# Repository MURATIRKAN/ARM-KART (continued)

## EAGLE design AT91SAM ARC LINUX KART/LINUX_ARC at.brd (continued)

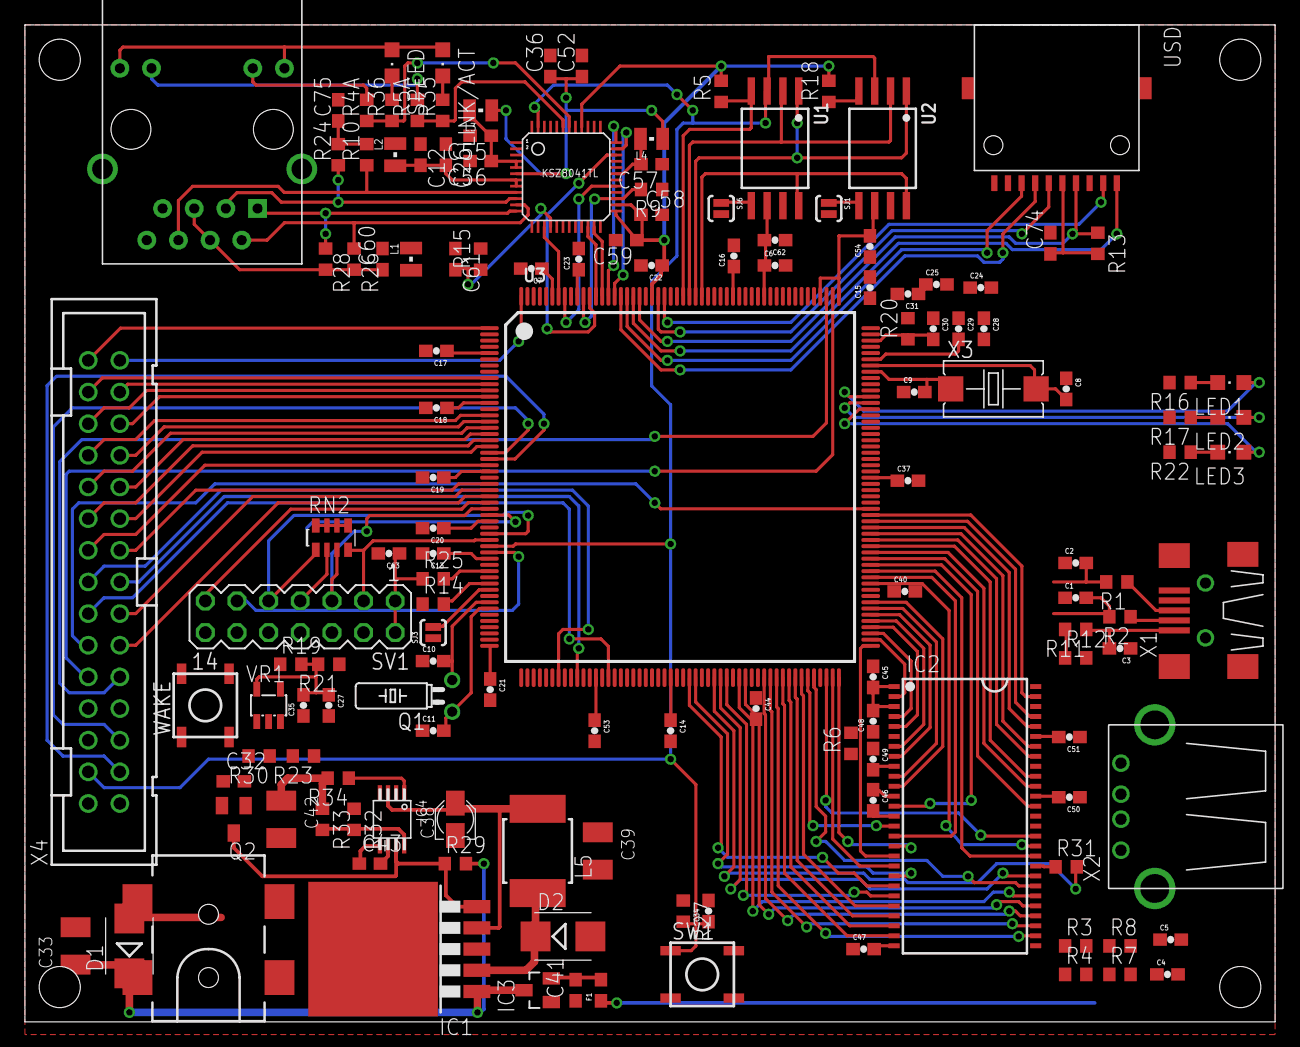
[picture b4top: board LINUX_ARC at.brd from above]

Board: 2 copper layers, 100.3 x 80.0 mm, 146 parts (1 on the bottom side), 154 nets.

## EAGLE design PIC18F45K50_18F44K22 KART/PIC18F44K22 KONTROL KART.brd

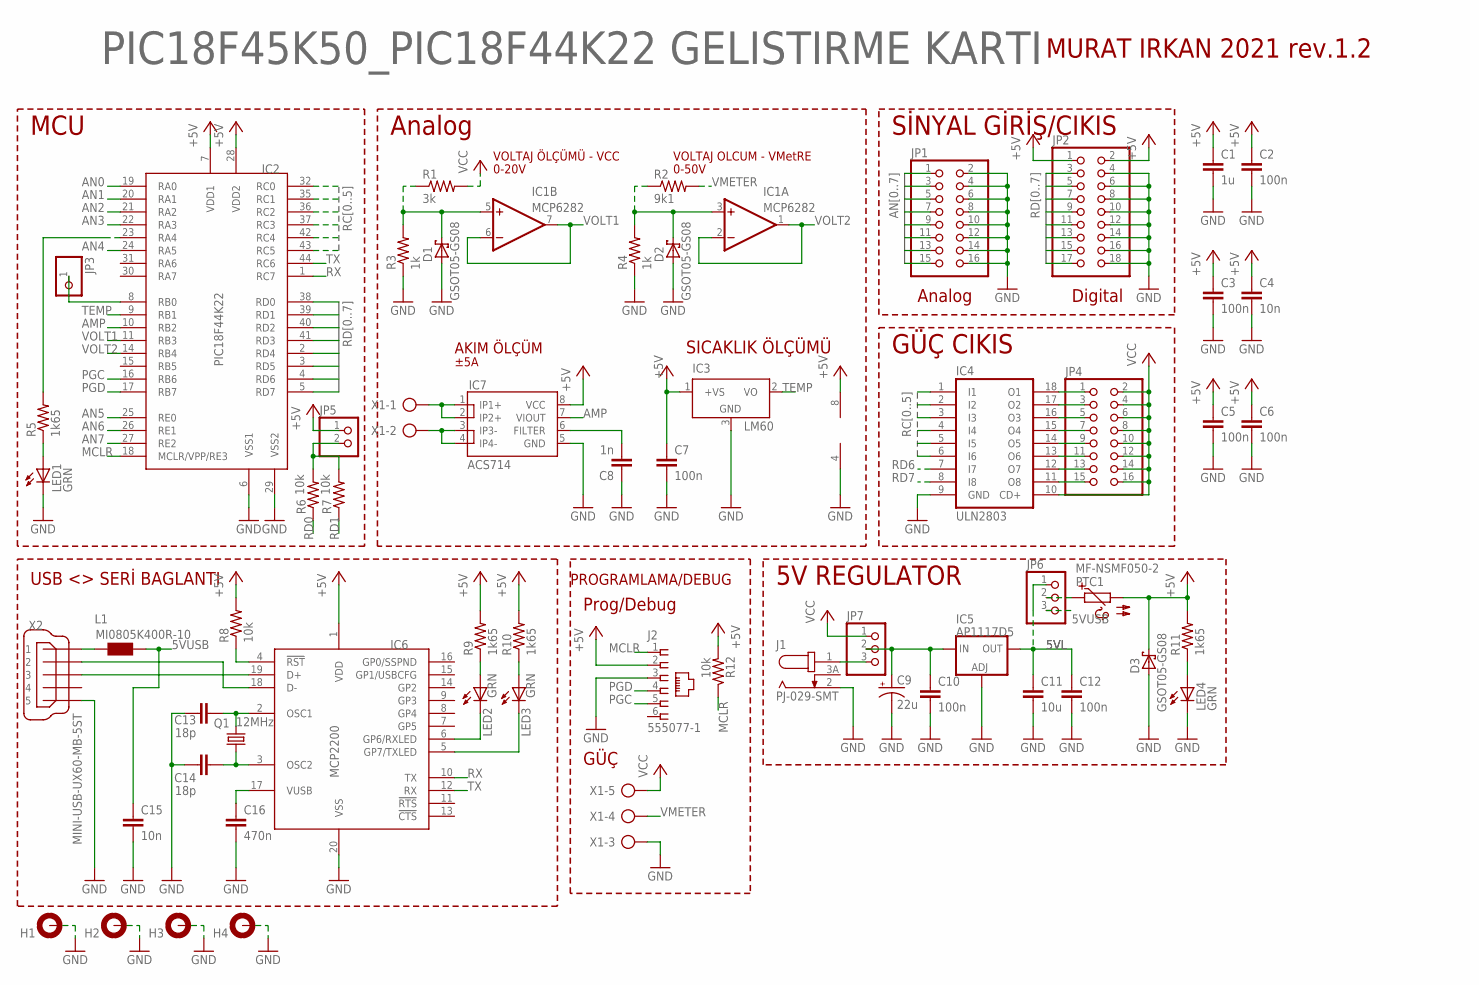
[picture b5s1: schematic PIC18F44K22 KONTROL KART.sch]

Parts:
C1: 1u; C0603
C2, C3, C5, C6, C7, C10, C12: 100n; C0603
C4, C15: 10n; C0603
C8: 1n; C0603
C9: 22u; 153CLV-0505
C11: 10u; C0805
C13, C14: 18p; C0603
C16: 470n; C0603
D1, D2, D3: GSOT05-GS08; SOT23
H1, H2, H3, H4: MOUNT-PAD-ROUND3.2; 3,2-PAD
IC1: MCP6282; SO08
IC2: PIC18F44K22; TQFP44
IC3: LM60; SOT23
IC4: ULN2803; SO18
IC5: AP1117D5; DPACK
IC6: MCP2200; SSOP20
IC7: ACS714; SO08
J1: PJ-029-SMT; SMT
J2: 555077-1
JP1, JP4: PINHD-2X8; 2X08
JP2: PINHD-2X9; 2X09
JP3: PINHD-1X1; 1X01
JP5: PINHD-1X2; 1X02
JP6, JP7: PINHD-1X3; 1X03
L1: MI0805K400R-10; 0805
LED1, LED2, LED3, LED4: GRN; CHIPLED_0603
PTC1: MF-NSMF050-2; 1206
Q1: 12MHz; HC49UP
R1: 3k; R0603
R2: 9k1; R0603
R3, R4: 1k; R0603
R5, R9, R10, R11: 1k65; R0603
R6, R7, R8, R12: 10k; R0603
X1: OSTTE-5
X2: MINI-USB-UX60-MB-5ST; UX60-MB-5ST

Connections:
5VL: C11.1, C12.1, IC5.4 (OUT), JP6.1
5VUSB: C15.1, JP6.3, L1.1
+5V: C1.1, C2.1, C3.1, C4.1, C5.1, C6.1, C7.1, D3.3 (C), IC1.8 (V+), IC2.7 (VDD1), IC2.28 (VDD2), IC3.1 (+VS), IC6.1 (VDD), IC7.8 (VCC), J2.2, JP2.1, JP2.2, JP5.1, PTC1.2, R8.2, R9.2, R10.2, R11.2, R12.2
ALIVE: IC2.23 (RA4), R5.2
AMP: IC2.10 (RB2), IC7.7 (VIOUT)
AN0: IC2.19 (RA0), JP1.15
AN1: IC2.20 (RA1), JP1.13
AN2: IC2.21 (RA2), JP1.11
AN3: IC2.22 (RA3), JP1.9
AN4: IC2.24 (RA5), JP1.7
AN5: IC2.25 (RE0), JP1.5
AN6: IC2.26 (RE1), JP1.3
AN7: IC2.27 (RE2), JP1.1
D+: IC6.19 (D+), X2.3
D-: IC6.18 (D-), X2.2
GND: C1.2, C2.2, C3.2, C4.2, C5.2, C6.2, C7.2, C8.1, C9.-, C10.2, C11.2, C12.2, C13.1, C14.1, C15.2, C16.2, D1.1 (A), D2.1 (A), D3.1 (A), H1.B3,2, H2.B3,2, H3.B3,2, H4.B3,2, IC1.4 (V-), IC2.6 (VSS1), IC2.29 (VSS2), IC3.3 (GND), IC4.9 (GND), IC5.1 (ADJ), IC6.20 (VSS), IC7.5 (GND), J1.2 (1), J2.3, JP1.2, JP1.4, JP1.6, JP1.8, JP1.10, JP1.12, JP1.14, JP1.16, JP2.4, JP2.6, JP2.8, JP2.10, JP2.12, JP2.14, JP2.16, JP2.18, LED1.C, LED4.C, R3.1, R4.1, X1.3, X2.5
IS1: IC7.1 (IP1+), IC7.2 (IP2+), X1.1
IS2: IC7.3 (IP3-), IC7.4 (IP4-), X1.2
MCLR: IC2.18 (MCLR/VPP/RE3), J2.1, R12.1
unnamed: C13.2, IC6.2 (OSC1), Q1.2
unnamed: C14.2, IC6.3 (OSC2), Q1.1
unnamed: JP5.2, R6.2, R7.2
unnamed: LED4.A, R11.1
unnamed: JP6.2, PTC1.1
unnamed: LED1.A, R5.1
unnamed: L1.2, X2.1
unnamed: C8.2, IC7.6 (FILTER)
unnamed: IC2.8 (RB0), JP3.1
unnamed: D1.3 (C), IC1.5 (+IN), R1.1, R3.2
unnamed: C9.+, C10.1, IC5.3 (IN), JP7.2
unnamed: D2.3 (C), IC1.3 (+IN), R2.1, R4.2
unnamed: IC6.4 (!RST), R8.1
unnamed: IC6.5 (GP7/TXLED), LED3.C
unnamed: IC6.6 (GP6/RXLED), LED2.C
unnamed: LED2.A, R9.1
unnamed: LED3.A, R10.1
unnamed: C16.1, IC6.17 (VUSB)
unnamed: J1.1 (3), JP7.3
P0: IC4.13 (O6), JP4.11
P1: IC4.14 (O5), JP4.9
P2: IC4.15 (O4), JP4.7
P3: IC4.16 (O3), JP4.5
P4: IC4.17 (O2), JP4.3
P5: IC4.18 (O1), JP4.1
PD6: IC4.12 (O7), JP4.13
PD7: IC4.11 (O8), JP4.15
PGC: IC2.16 (RB6), J2.5
PGD: IC2.17 (RB7), J2.4
RC0: IC2.32 (RC0), IC4.6 (I6)
RC1: IC2.35 (RC1), IC4.5 (I5)
RC2: IC2.36 (RC2), IC4.4 (I4)
RC3: IC2.37 (RC3), IC4.3 (I3)
RC4: IC2.42 (RC4), IC4.2 (I2)
RC5: IC2.43 (RC5), IC4.1 (I1)
RD0: IC2.38 (RD0), JP2.17, R6.1
RD1: IC2.39 (RD1), JP2.15, R7.1
RD2: IC2.40 (RD2), JP2.13
RD3: IC2.41 (RD3), JP2.11
RD4: IC2.2 (RD4), JP2.9
RD5: IC2.3 (RD5), JP2.7
RD6: IC2.4 (RD6), IC4.7 (I7), JP2.5
RD7: IC2.5 (RD7), IC4.8 (I8), JP2.3
RX: IC2.1 (RC7), IC6.10 (TX)
TEMP: IC2.9 (RB1), IC3.2 (VO)
TX: IC2.44 (RC6), IC6.12 (RX)
VCC: IC4.10 (CD+), JP4.2, JP4.4, JP4.6, JP4.8, JP4.10, JP4.12, JP4.14, JP4.16, JP7.1, R1.2, X1.5
VMETER: R2.2, X1.4
VOLT1: IC1.6 (-IN), IC1.7 (OUT), IC2.11 (RB3)
VOLT2: IC1.1 (OUT), IC1.2 (-IN), IC2.14 (RB4)

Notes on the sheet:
5V REGULATOR
USB <> SERİ BAGLANTI
VOLTAJ ÖLÇÜMÜ - VCC
VOLTAJ OLCUM - VMetRE
AKIM ÖLÇÜM
SICAKLIK ÖLÇÜMÜ
Analog
MCU
SİNYAL GİRİŞ/CIKIS
Digital
GÜÇ CIKIS
PROGRAMLAMA/DEBUG
Prog/Debug
GÜÇ
0-20V
0-50V
±5A
PIC18F45K50_PIC18F44K22 GELISTIRME KARTI
MURAT IRKAN 2021 rev.1.2

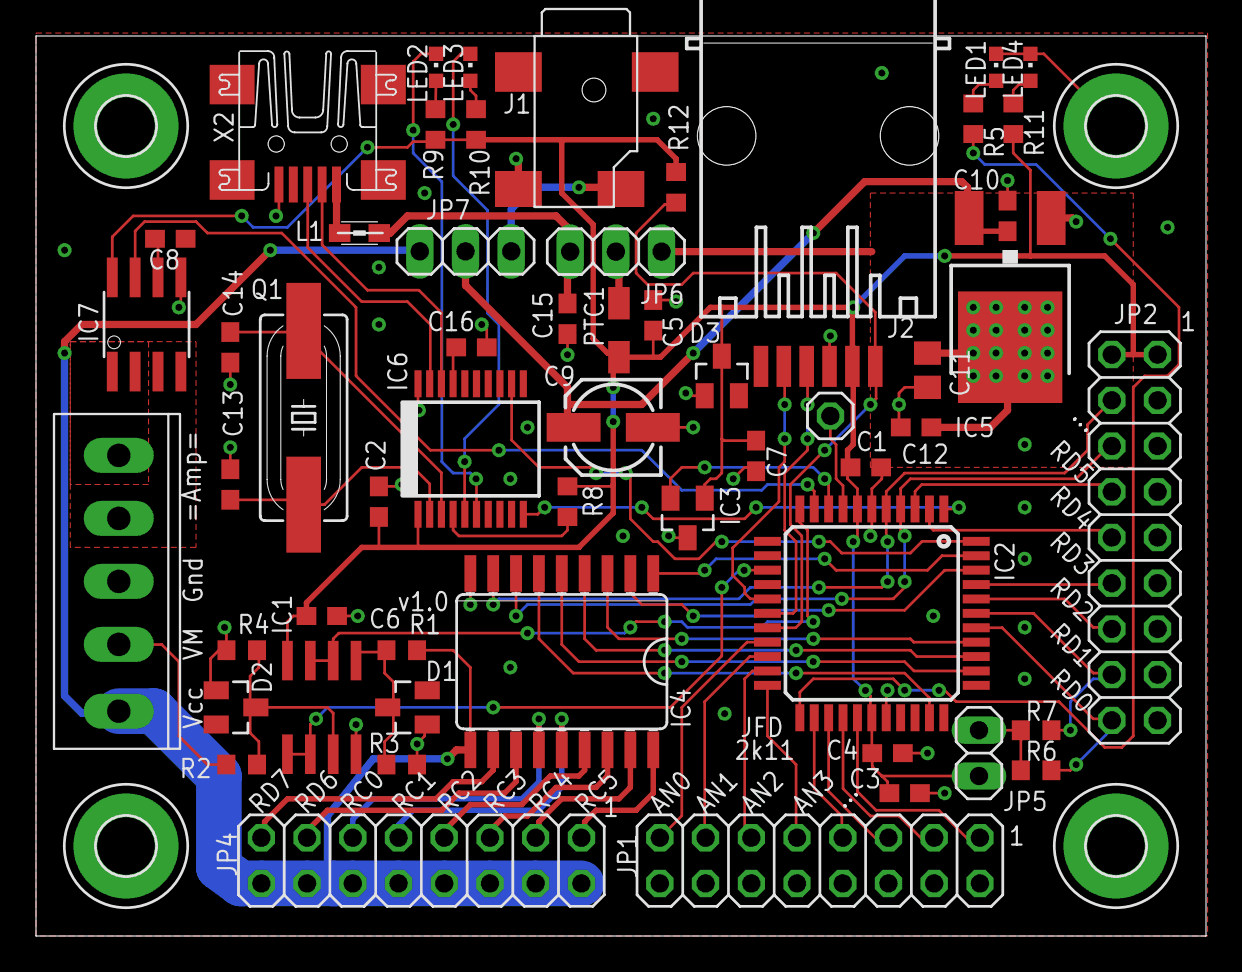
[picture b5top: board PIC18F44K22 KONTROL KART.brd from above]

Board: 2 copper layers, 65.0 x 50.0 mm, 60 parts (0 on the bottom side), 69 nets.

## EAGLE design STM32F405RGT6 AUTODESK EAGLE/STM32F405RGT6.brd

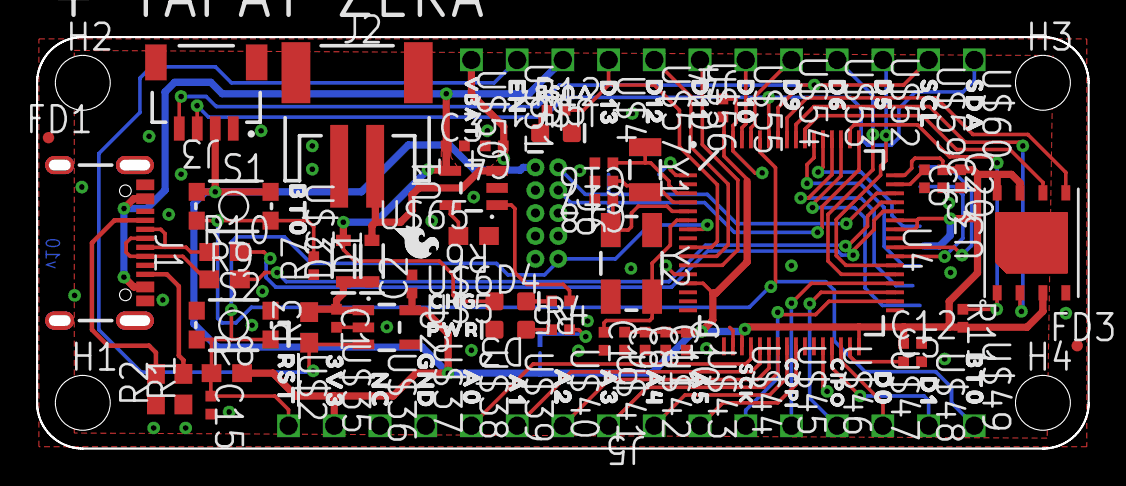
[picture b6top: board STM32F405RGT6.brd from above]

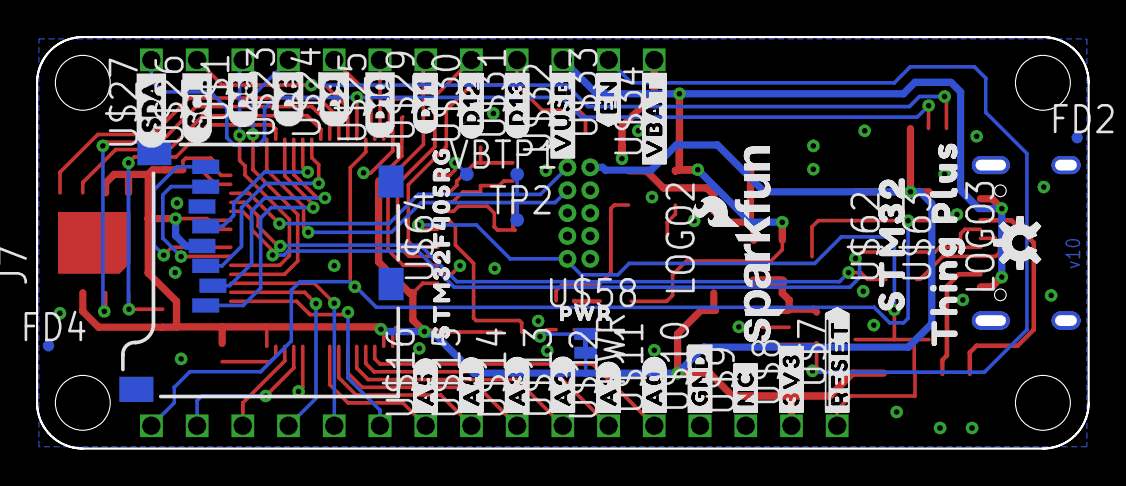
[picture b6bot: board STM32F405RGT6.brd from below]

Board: 2 copper layers, 58.4 x 22.9 mm, 123 parts (35 on the bottom side), 58 nets.

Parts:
C1, C2, C9: 1.0uF; 0402-TIGHT
C3, C4, C10: 4.7uF; 0402-TIGHT
C5, C6: 2.2uF; 0402-TIGHT
C8, C11, C12, C13, C14, C15, C20: 0.1uF; 0402-TIGHT
C16, C17: 15pF; 0402-TIGHT
C18, C19: 22pF; 0402-TIGHT
D1, D2: 3A/10V/280mV; SOD-323
D3: RED; LED-0603
D4: Yellow; LED-0603
D5: BLUE; LED-0603
FD1, FD3: FIDUCIALUFIDUCIAL; FIDUCIAL-MICRO
FD2, FD4: FIDUCIALUFIDUCIAL; FIDUCIAL-MICRO_FD2
H1, H2, H3, H4: STAND-OFFTIGHT; STAND-OFF-TIGHT
J1: USB-C-16P-2LAYER-PADS
J2: JST-2-SMD
J3: QWIIC_RA; JST04_1MM_RA
J4: 1X12_SM_SQ_NOSILK
J5: 1X16_SM_SQ_NOSILK
J6: CORTEX_DEBUG; 2X5-PTH-1.27MM-NO_SILK
J7: MICRO-SD; MICRO-SD-SOCKET
LOGO2: SFE_LOGO_NAME_FLAME.1_INCH; SFE_LOGO_NAME_FLAME_.1
LOGO3: OSHW-LOGOS; OSHW-LOGO-S
PWR: SMT-JUMPER_2_NC_TRACE_NO-SILK
R1, R2: 5.1k; 0603
R3: 10k; 0603
R4, R5, R12: 1k; 0402-TIGHT
R6: 2.0k; 0603
R7, R11: 100k; 0402-TIGHT
R8: 4.7k; 0603
R9, R10: 22; 0603
S1, S2: TACTILE_SWITCH_SMD_4.6X2.8MM
TP1, TP2: PAD.03X.03
U1: MCP73831; SOT23-5
U2: 3.3V; SOT23-5
U3: W25QXX128MBIT-6X5; WSON-8-6X5
U4: STM32F405RGT6; TQFP64
U$1: D53
U$2: #RST#0
U$3, U$49: BT00
U$4: D130
U$5: PWR0
U$6: CHG0
U$7: ##RESET##0
U$8: #3V3#0
U$9: #NC#0
U$10: #GND#0
U$11: #A0#0
U$12: #A1#0
U$13: #A2#0
U$14: #A3#0
U$15: #A4#0
U$16: #A5#0
U$23: D62
U$24: D91
U$25: D100; D100_U$25
U$26: SCL4
U$27: U$27; SDA5
U$29: #D11#0
U$30: #D12#0
U$31: #D13#0
U$32: #VUSB#0
U$33: #EN#0
U$34: #VBAT#0
U$35: 3V30
U$36: NC0
U$37: GND0
U$38: A00
U$39: A10
U$40: A20
U$41: A30
U$42: A40
U$43: A50
U$44: SCK0
U$45: COPI0
U$46: CIPO0
U$47: D00
U$48: D10
U$50: VBAT_0
U$51: EN_0
U$52: D50
U$53: D60
U$54: D90
U$55: D100
U$56: D110
U$57: D120
U$58: PWR0; PWR0_U$58
U$59: SCL_0
U$60: SDA_0
U$61: VUSB0
U$62: STM320
U$63: THING_PLUS0
U$64: STM32F405RG0
U$65: SFE_LOGO_FLAME_.1
VB: PAD.03X.03
Y1: 32.768kHz; CRYSTAL-SMD-3.2X1.5MM
Y2: 12MHz; CRYSTAL-SMD-5X3.2-4PAD

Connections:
3.3V: C2.1, C8.1, C9.1, C10.1, C11.1, C12.1, C13.1, C14.1, C20.1, J3.2, J5.15, J6.1, J7.VCC, PWR.2, R8.2, R11.2, S1.3, S1.4, U2.5, U3.3, U3.7, U3.8, U4.13, U4.19, U4.32, U4.42, U4.43, U4.48, U4.64
32KHZ_IN: C16.1, U4.3, Y1.P$1
32KHZ_OUT: C17.1, U4.4, Y1.P$2
!RESET: C15.1, J5.16, J6.10, R8.1, S2.1, S2.2, U4.7
A0: J5.12, U4.20
A1: J5.11, U4.21
A2: J5.10, U4.22
A3: J5.9, U4.23
A4: J5.8, U4.24
A5: J5.7, U4.25
BOOT0: J5.1, R7.2, S1.1, S1.2, U4.60
CIPO: J5.4, U4.35
COPI: J5.5, U4.36
D0/RX: J5.3, U4.30
D1/TX: J5.2, U4.29
D5: J4.3, U4.38
D6: J4.4, U4.37
D9: J4.5, U4.61
D10: J4.6, U4.62
D11: J4.7, U4.11
D12: J4.8, U4.10
D13: J4.9, R12.2, U4.9
D+: R9.2, U4.45
D-: R10.2, U4.44
EN: J4.11, R3.1, U2.3
FLASH_!CS: R11.1, U3.1, U4.50
FLASH_SCK: U3.6, U4.55
FLASH_SDI: U3.5, U4.57
FLASH_SDO: U3.2, U4.56
GND: C1.2, C2.2, C3.2, C4.2, C5.2, C6.2, C8.2, C9.2, C10.2, C11.2, C12.2, C13.2, C14.2, C15.2, C16.2, C17.2, C18.2, C19.2, C20.2, D3.C, D5.C, J1.GND, J1.GND2, J1.SHLD1, J1.SHLD2, J1.SHLD3, J1.SHLD4, J2.1, J3.1, J5.13, J6.3, J6.5, J6.9, J7.CD1, J7.GND, J7.GND1, J7.GND3, R1.1, R2.1, R6.1, R7.1, S2.3, S2.4, U1.2, U2.2, U3.4, U4.12, U4.18, U4.28, U4.63
unnamed: PWR.1, R4.2
unnamed: J1.A6, J1.B6, R9.1
unnamed: J1.A7, J1.B7, R10.1
unnamed: D3.A, R4.1
unnamed: R6.2, U1.5
unnamed: J1.A5, R2.2
unnamed: J1.B5, R1.2
unnamed: D4.C, R5.2
unnamed: R5.1, U1.1
unnamed: C5.1, U4.31
unnamed: C6.1, U4.47
OSC_IN: C18.1, U4.5, Y2.1
OSC_OUT: C19.1, U4.6, Y2.3
SCK: J5.6, U4.34
SCL: J3.4, J4.2, U4.58
SDA: J3.3, J4.1, U4.59
SDIO_CLK: J7.SCLK, U4.53
SDIO_CMD: J7.DI/CMD, U4.54
SDIO_D0: J7.DO/DAT0, U4.39
SDIO_D1: J7.DAT1, U4.40
SDIO_D2: J7.DAT2, U4.51
SDIO_D3: J7.CS/DAT3, U4.52
SWCLK: J6.4, TP2.P$1, U4.49
SWDIO: J6.2, TP1.P$1, U4.46
VB: U4.1, VB.P$1
VIN: C1.1, D1.C, D2.C, R3.2, U2.1
V_BATT: C4.1, D1.A, J2.2, J4.12, U1.3
V_USB: C3.1, D2.A, D4.A, J1.VBUS1, J1.VBUS2, J4.10, U1.4

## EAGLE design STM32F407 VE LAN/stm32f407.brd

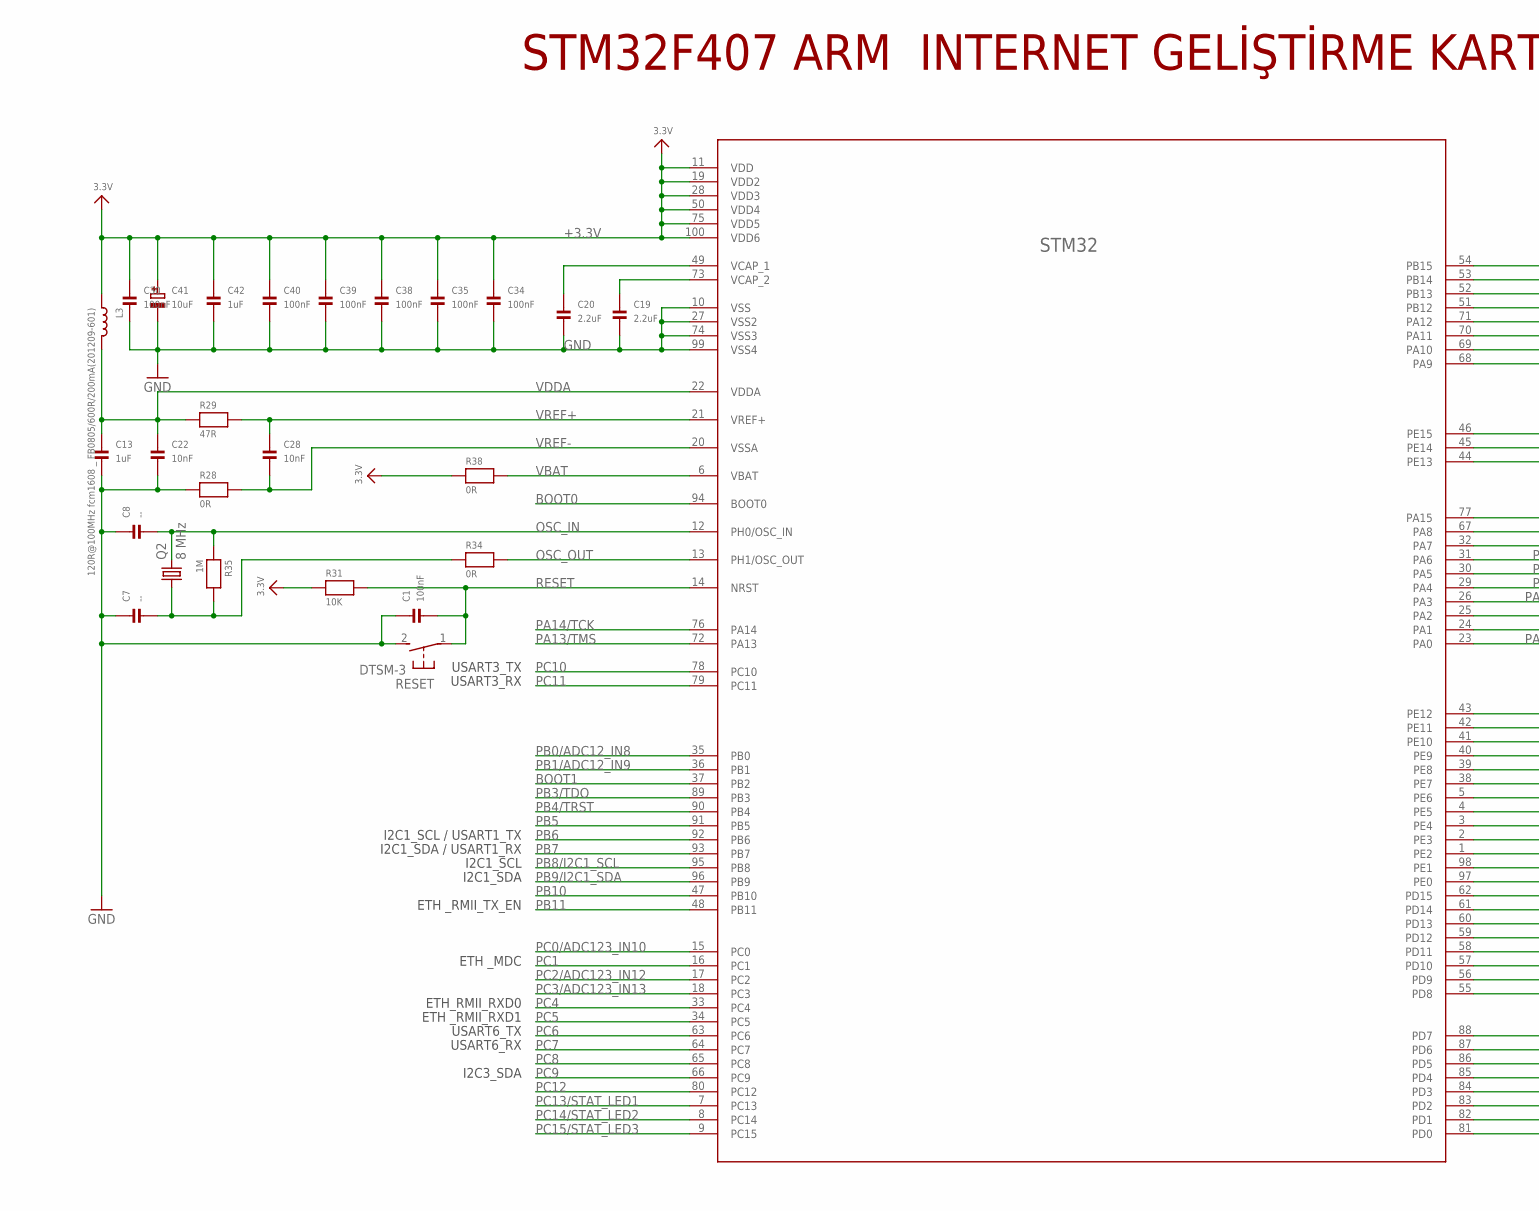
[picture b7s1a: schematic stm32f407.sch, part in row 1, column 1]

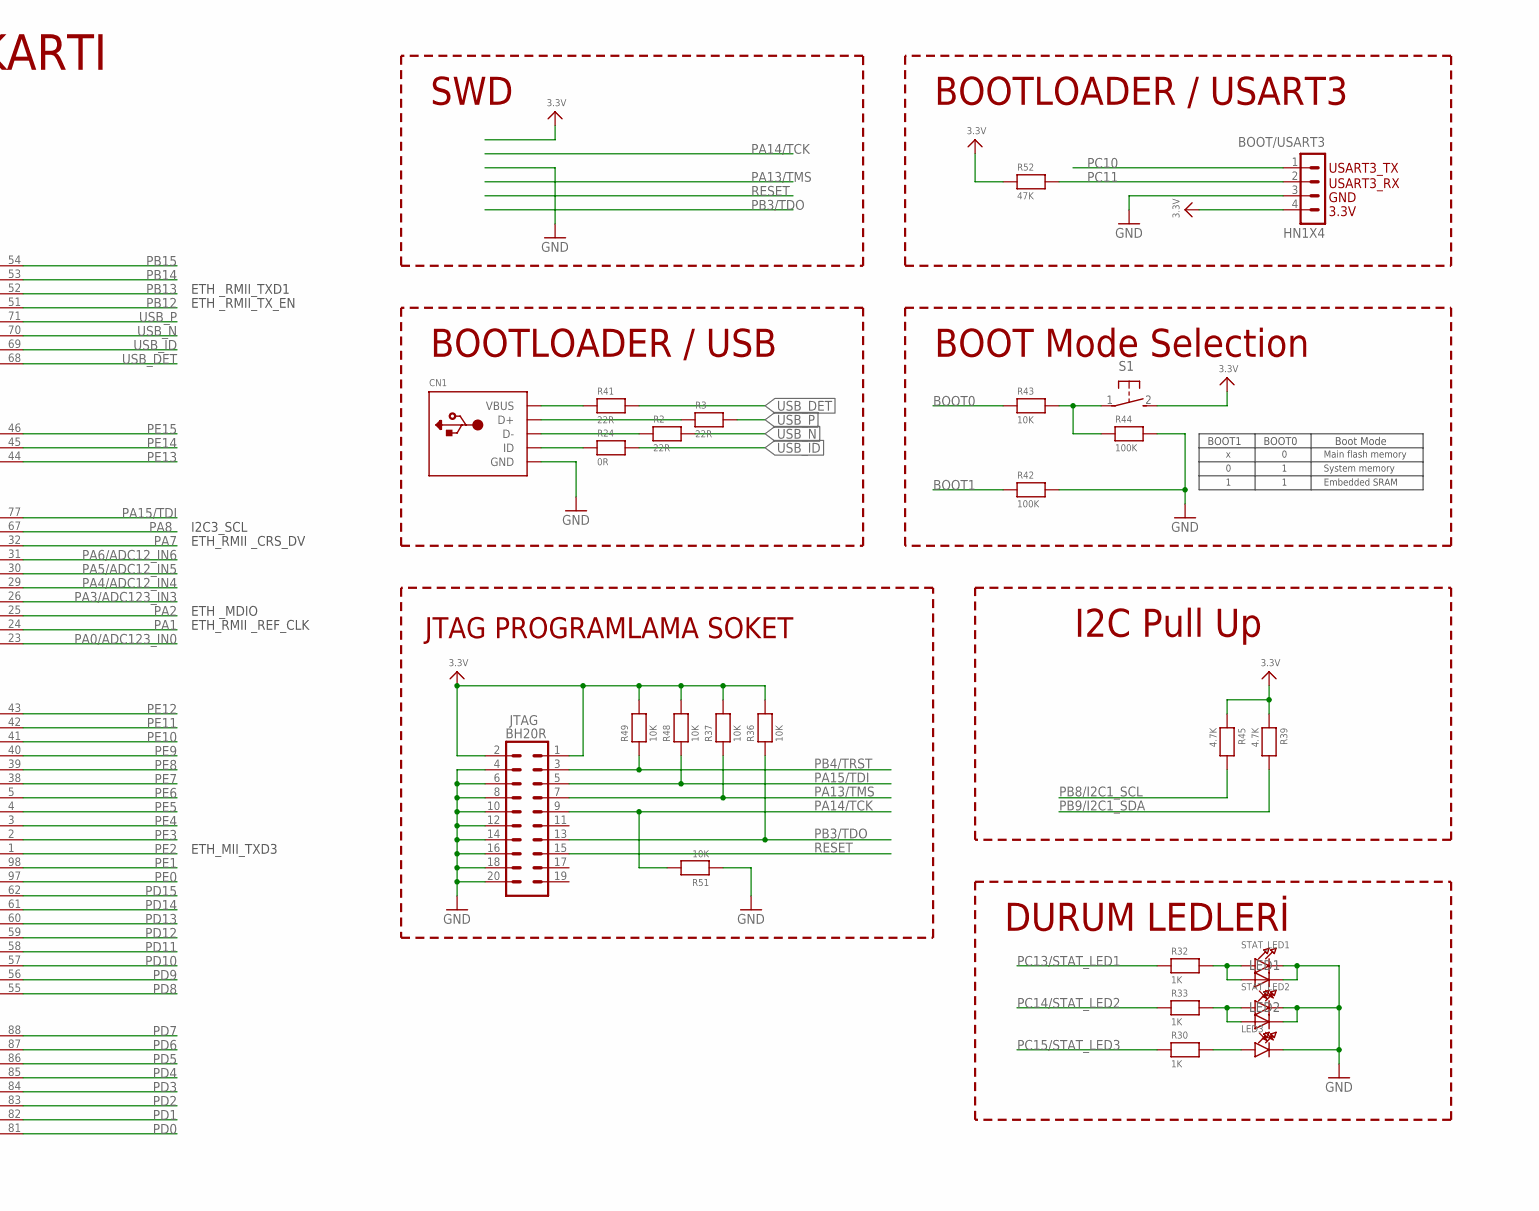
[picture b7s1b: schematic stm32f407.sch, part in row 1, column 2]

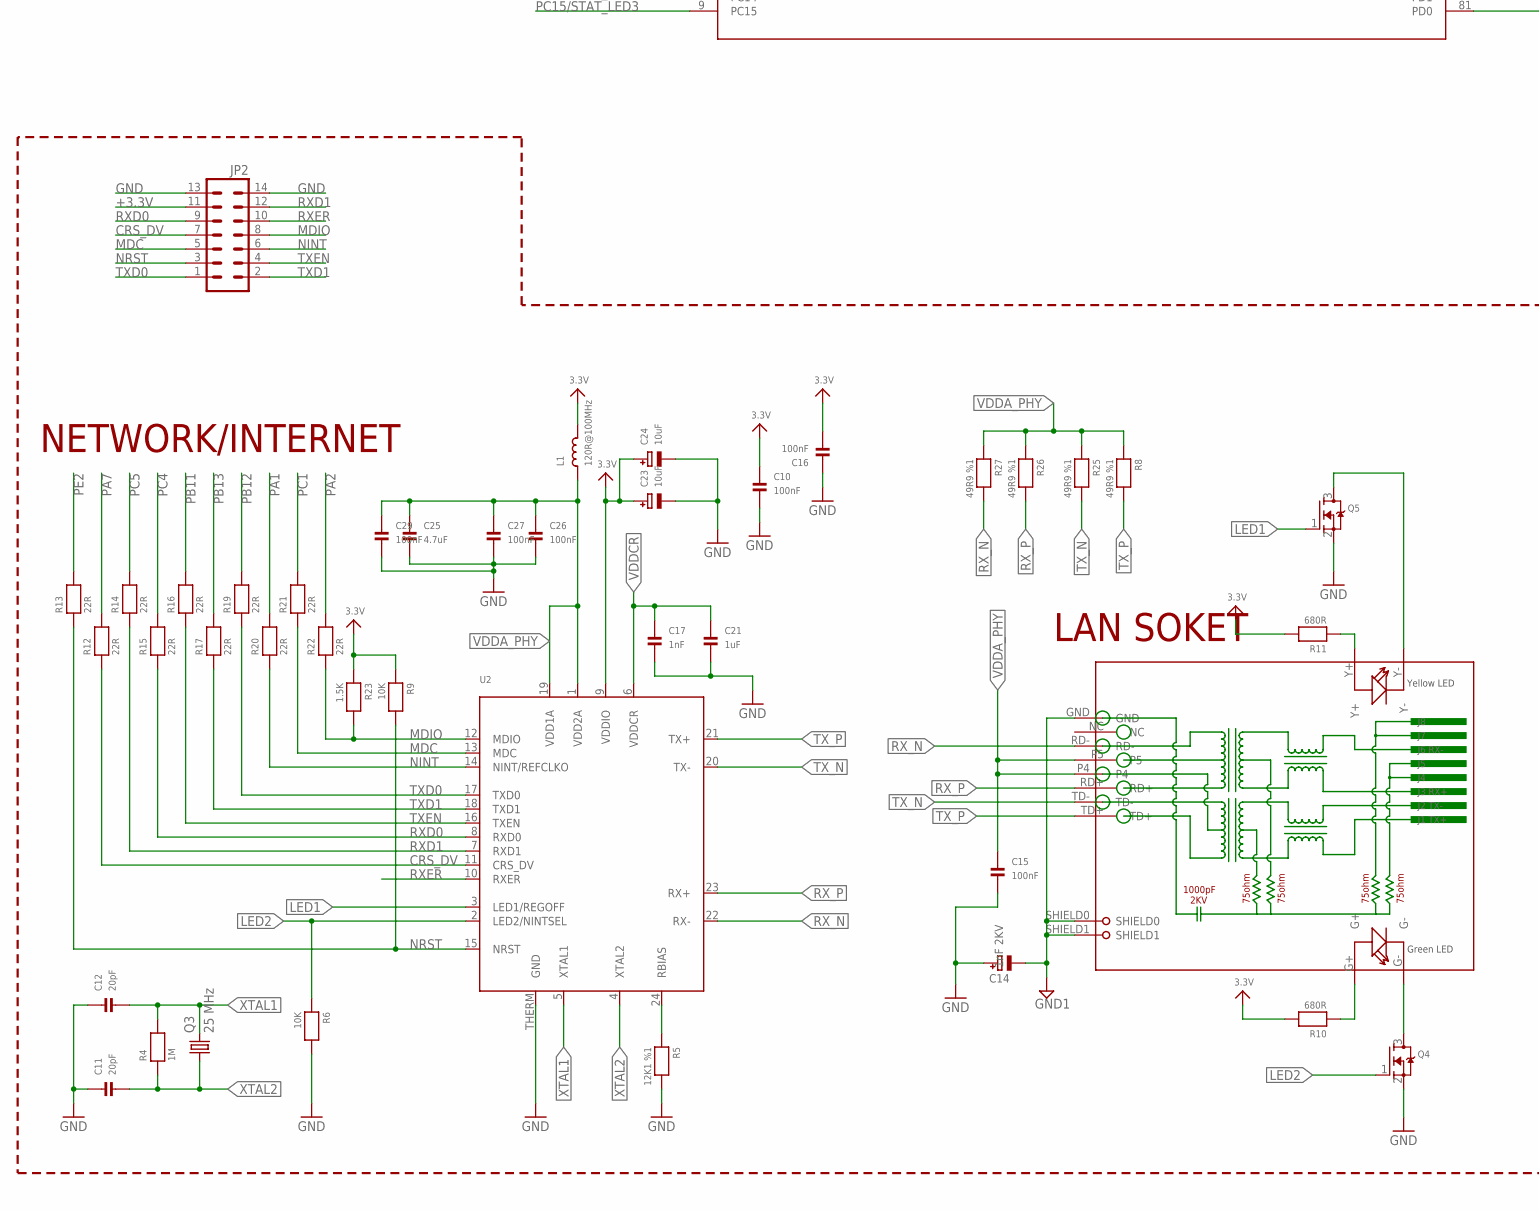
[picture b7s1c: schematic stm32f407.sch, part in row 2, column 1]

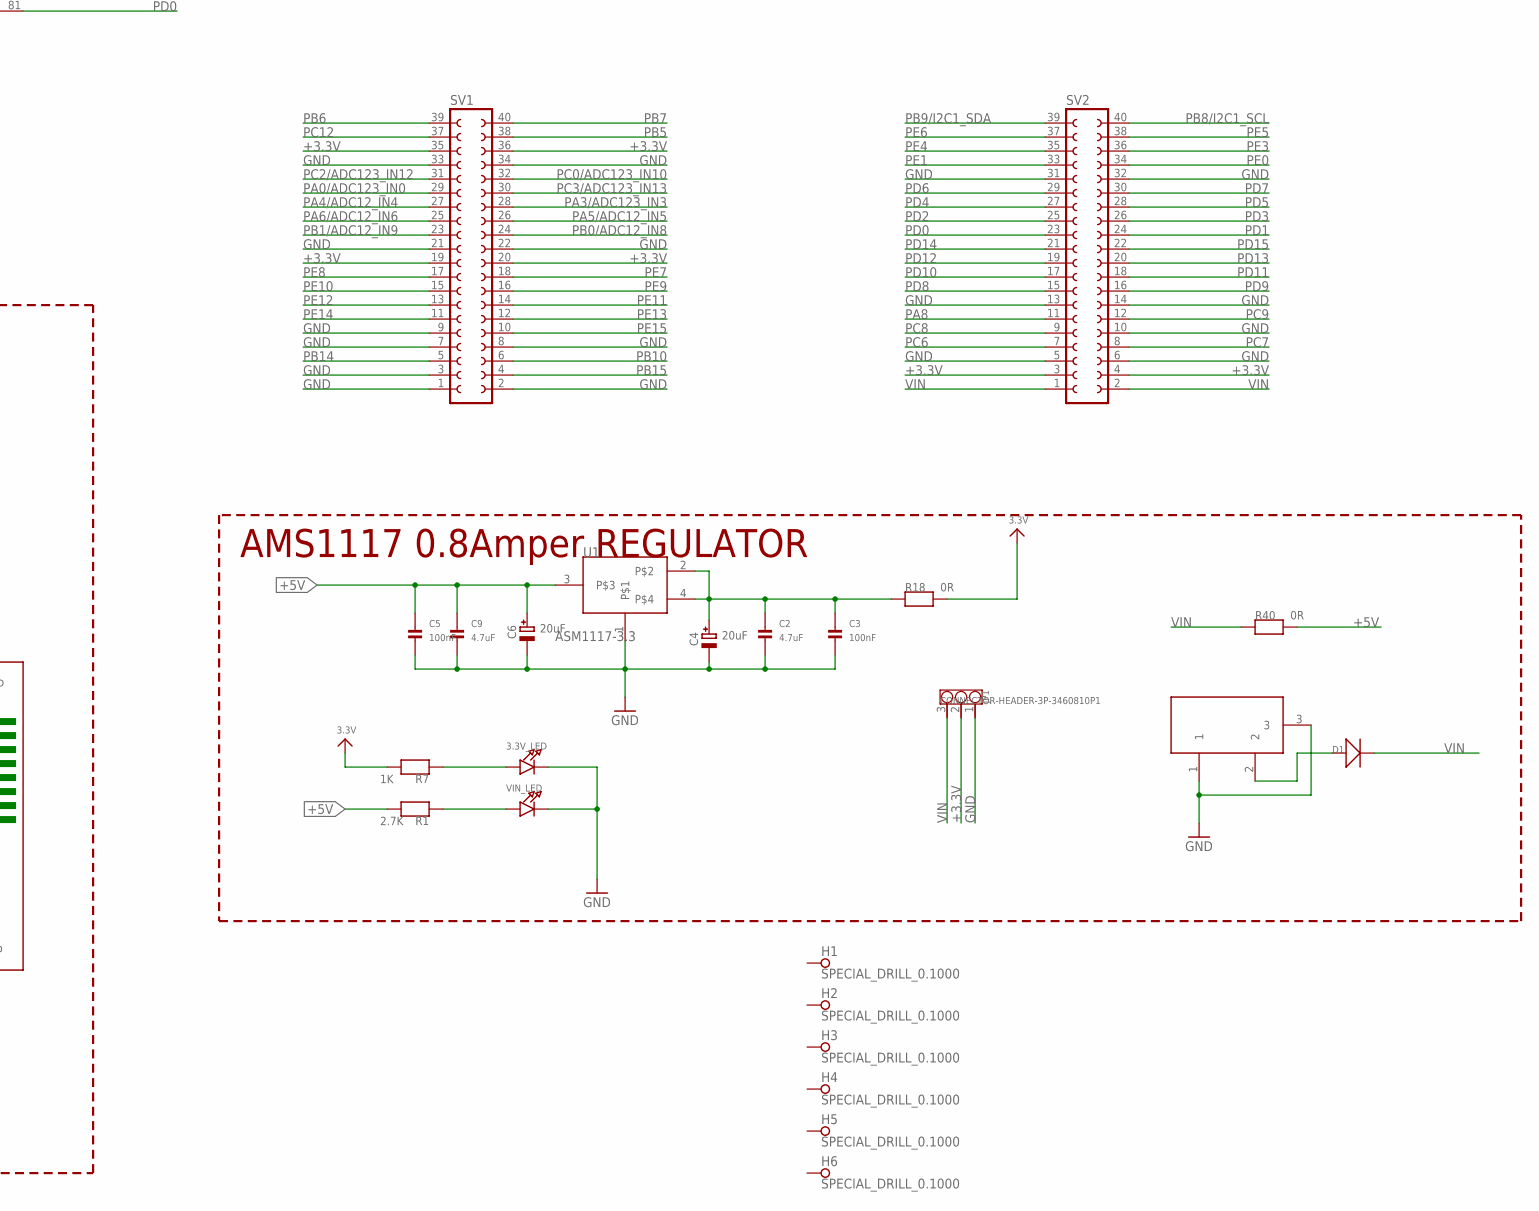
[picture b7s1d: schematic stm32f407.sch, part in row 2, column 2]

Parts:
3.3V_LED: LED0805; CHIPLED_0805
BOOT/USART3: HN1X4
C1, C10, C16, C26, C27, C29, C30, C34, C35, C38, C39, C40: 100nF; _0603
C2, C9: 4.7uF; 0805
C3, C5: 100nF; 0805
C4, C6: 20uF; EIA3528-21/B-R
C7, C8: --; _0603
C11, C12: 20pF; _0603
C13, C21, C42: 1uF; _0805
C14: 1nF 2KV; EIA3528-21/B-R
C15: 100nF; _0805
C17: 1nF; _0603
C19, C20: 2.2uF; 1206
C22, C28: 10nF; _0603
C23, C24, C41: 10uF; EIA3528-21/B-R
C25: 4.7uF; _0805
CN1: USBMINIBLARGE; USB-MINIB_LARGER
D1: D-D1206; LL-34
H1, H2, H3, H4, H5, H6: SPECIAL_DRILL_0.1000; PAD_0.1000
JP1: CONNECTOR-HEADER-3P-3460810P1; 1X3P-2.54-2.54-11.6-3.0-BLACK-MALE
JP2: MA07-2
JTAG: BH20R
L1: 120R@100MHz; _0805
L3: 120R@100MHz fcm1608 _ FB0805/600R/200mA(201209-60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; _0805
LED1, LED2: LED5MM
LED3: LED0805; CHIPLED_0805
Q2: 8 MHz; HC49UP
Q3: 25 MHz; HC49UP
Q4, Q5: MOSFET-NWIDE; SOT23-WIDE
R1: 2.7K; _0603
R2, R3, R12, R13, R14, R15, R16, R17, R19, R20, R21, R22, R41: 22R; _0603
R4, R35: 1M; _0603
R5: 12K1 %1; _0603
R6, R9, R31, R36, R37, R43, R48, R49, R51: 10K; _0603
R7, R30, R32, R33: 1K; _0603
R8, R25, R26, R27: 49R9 %1; _0603
R10, R11: 680R; _0805
R18, R40: 0R; 0805
R23: 1.5K; _0603
R24, R28, R34, R38: 0R; _0603
R29: 47R; _0603
R39, R45: 4.7K; 1206
R42, R44: 100K; _0603
R52: 47K; _0603
RESET: DTSM-3
RJ1: HR911105A
S1: 31-XX; B3F-31XX
STAT_LED1, STAT_LED2: LED0805; CHIPLED_0805
STM32: STM32F407; 100LQFP
SV1, SV2: FE20-2
U1: ASM1117-3.3; SOT223
U2: LAN8720; QFN24_4MM
VIN_LED: LED0805; CHIPLED_0805
X1: DC21MMX; DC-21MM

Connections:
+3.3V: BOOT/USART3.4, C10.1, C16.2, C23.+, C24.+, C30.1, C34.1, C35.1, C38.1, C39.1, C40.1, C41.+, C42.1, JP1.2, JP2.11, JTAG.1, JTAG.2, L1.2, L3.1, R7.2, R9.1, R10.2, R11.2, R18.2, R23.1, R31.1, R36.2, R37.2, R38.1, R39.1, R45.1, R48.2, R49.2, R52.1, S1.2 (S), STM32.11 (VDD), STM32.19 (VDD2), STM32.28 (VDD3), STM32.50 (VDD4), STM32.75 (VDD5), STM32.100 (VDD6), SV1.19, SV1.20, SV1.35, SV1.36, SV2.3, SV2.4, U2.9 (VDDIO)
+5V: C5.1, C6.+, C9.1, R1.2, R40.2, U1.3
BOOT0: R43.1, STM32.94 (BOOT0)
BOOT1: R42.1, STM32.37 (PB2)
CRS_DV: JP2.7, R12.1, U2.11 (CRS_DV)
GND: 3.3V_LED.C, BOOT/USART3.3, C1.1, C2.2, C3.2, C4.-, C5.2, C6.-, C7.1, C8.1, C9.2, C10.2, C11.1, C12.1, C13.2, C14.+, C15.2, C16.1, C17.2, C19.2, C20.2, C21.2, C22.2, C23.-, C24.-, C25.2, C26.2, C27.2, C29.2, C30.2, C34.2, C35.2, C38.2, C39.2, C40.2, C41.-, C42.2, CN1.GND, JP1.1, JP2.13, JP2.14, JTAG.4, JTAG.6, JTAG.8, JTAG.10, JTAG.12, JTAG.14, JTAG.16, JTAG.18, JTAG.20, LED1.K (C), LED2.K (C), LED3.C, Q4.2 (S), Q5.2 (S), R5.2, R6.2, R28.1, R42.2, R44.2, R51.1, RESET.2, STAT_LED1.C, STAT_LED2.C, STM32.10 (VSS), STM32.27 (VSS2), STM32.74 (VSS3), STM32.99 (VSS4), SV1.1, SV1.2, SV1.3, SV1.7, SV1.8, SV1.9, SV1.21, SV1.22, SV1.33, SV1.34, SV2.5, SV2.6, SV2.10, SV2.13, SV2.14, SV2.31, SV2.32, U1.1, U2.THERM (GND), VIN_LED.C, X1.1, X1.3
GND1: C14.-, RJ1.GND, RJ1.SHIELD0, RJ1.SHIELD1
LED1: Q5.1 (G), U2.3 (LED1/REGOFF)
LED2: Q4.1 (G), R6.1, U2.2 (LED2/NINTSEL)
MDC: JP2.5, R21.1, U2.13 (MDC)
MDIO: JP2.8, R22.1, R23.2, U2.12 (MDIO)
unnamed: LED1.A, R32.2, STAT_LED1.A
unnamed: LED2.A, R33.2, STAT_LED2.A
unnamed: CN1.VBUS, R41.1
unnamed: LED3.A, R30.2
unnamed: D1.A (+), X1.2
unnamed: C2.1, C3.1, C4.+, R18.1, U1.2, U1.4
unnamed: 3.3V_LED.A, R7.1
unnamed: R43.2, R44.1, S1.1
unnamed: CN1.ID, R24.1
unnamed: R1.1, VIN_LED.A
unnamed: CN1.D+, R3.1
unnamed: R5.1, U2.24 (RBIAS)
unnamed: R10.1, RJ1.G+
unnamed: R11.1, RJ1.Y+
unnamed: Q4.3 (D), RJ1.G-
unnamed: Q5.3 (D), RJ1.Y-
unnamed: CN1.D-, R2.1
unnamed: C19.1, STM32.73 (VCAP_2)
unnamed: C20.1, STM32.49 (VCAP_1)
unnamed: C7.2, Q2.1, R34.1, R35.2
NINT: JP2.6, R20.1, U2.14 (NINT/REFCLKO)
NRST: JP2.3, R9.2, R13.1, U2.15 (NRST)
OSC_IN: C8.2, Q2.2, R35.1, STM32.12 (PH0/OSC_IN)
OSC_OUT: R34.2, STM32.13 (PH1/OSC_OUT)
PA0/ADC123_IN0: STM32.23 (PA0), SV1.29
PA1: R20.2, STM32.24 (PA1)
PA2: R22.2, STM32.25 (PA2)
PA3/ADC123_IN3: STM32.26 (PA3), SV1.28
PA4/ADC12_IN4: STM32.29 (PA4), SV1.27
PA5/ADC12_IN5: STM32.30 (PA5), SV1.26
PA6/ADC12_IN6: STM32.31 (PA6), SV1.25
PA7: R12.2, STM32.32 (PA7)
PA8: STM32.67 (PA8), SV2.11
PA13/TMS: JTAG.7, R37.1, STM32.72 (PA13)
PA14/TCK: JTAG.9, R51.2, STM32.76 (PA14)
PA15/TDI: JTAG.5, R48.1, STM32.77 (PA15)
PB0/ADC12_IN8: STM32.35 (PB0), SV1.24
PB1/ADC12_IN9: STM32.36 (PB1), SV1.23
PB3/TDO: JTAG.13, R36.1, STM32.89 (PB3)
PB4/TRST: JTAG.3, R49.1, STM32.90 (PB4)
PB5: STM32.91 (PB5), SV1.38
PB6: STM32.92 (PB6), SV1.39
PB7: STM32.93 (PB7), SV1.40
PB8/I2C1_SCL: R45.2, STM32.95 (PB8), SV2.40
PB9/I2C1_SDA: R39.2, STM32.96 (PB9), SV2.39
PB10: STM32.47 (PB10), SV1.6
PB11: R16.2, STM32.48 (PB11)
PB12: R19.2, STM32.51 (PB12)
PB13: R17.2, STM32.52 (PB13)
PB14: STM32.53 (PB14), SV1.5
PB15: STM32.54 (PB15), SV1.4
PC0/ADC123_IN10: STM32.15 (PC0), SV1.32
PC1: R21.2, STM32.16 (PC1)
PC2/ADC123_IN12: STM32.17 (PC2), SV1.31
PC3/ADC123_IN13: STM32.18 (PC3), SV1.30
PC4: R15.2, STM32.33 (PC4)
PC5: R14.2, STM32.34 (PC5)
PC6: STM32.63 (PC6), SV2.7
PC7: STM32.64 (PC7), SV2.8
PC8: STM32.65 (PC8), SV2.9
PC9: STM32.66 (PC9), SV2.12
PC10: BOOT/USART3.1, STM32.78 (PC10)
PC11: BOOT/USART3.2, R52.2, STM32.79 (PC11)
PC12: STM32.80 (PC12), SV1.37
PC13/STAT_LED1: R32.1, STM32.7 (PC13)
PC14/STAT_LED2: R33.1, STM32.8 (PC14)
PC15/STAT_LED3: R30.1, STM32.9 (PC15)
PD0: STM32.81 (PD0), SV2.23
PD1: STM32.82 (PD1), SV2.24
PD2: STM32.83 (PD2), SV2.25
PD3: STM32.84 (PD3), SV2.26
PD4: STM32.85 (PD4), SV2.27
PD5: STM32.86 (PD5), SV2.28
PD6: STM32.87 (PD6), SV2.29
PD7: STM32.88 (PD7), SV2.30
PD8: STM32.55 (PD8), SV2.15
PD9: STM32.56 (PD9), SV2.16
PD10: STM32.57 (PD10), SV2.17
PD11: STM32.58 (PD11), SV2.18
PD12: STM32.59 (PD12), SV2.19
PD13: STM32.60 (PD13), SV2.20
PD14: STM32.61 (PD14), SV2.21
PD15: STM32.62 (PD15), SV2.22
PE0: STM32.97 (PE0), SV2.34
PE1: STM32.98 (PE1), SV2.33
PE2: R13.2, STM32.1 (PE2)
PE3: STM32.2 (PE3), SV2.36
PE4: STM32.3 (PE4), SV2.35
PE5: STM32.4 (PE5), SV2.38
PE6: STM32.5 (PE6), SV2.37
PE7: STM32.38 (PE7), SV1.18
PE8: STM32.39 (PE8), SV1.17
PE9: STM32.40 (PE9), SV1.16
PE10: STM32.41 (PE10), SV1.15
PE11: STM32.42 (PE11), SV1.14
PE12: STM32.43 (PE12), SV1.13
PE13: STM32.44 (PE13), SV1.12
PE14: STM32.45 (PE14), SV1.11
PE15: STM32.46 (PE15), SV1.10
RESET: C1.2, JTAG.15, R31.2, RESET.1, STM32.14 (NRST)
RXD0: JP2.9, R15.1, U2.8 (RXD0)
RXD1: JP2.12, R14.1, U2.7 (RXD1)
RXER: JP2.10, U2.10 (RXER)
RX_N: R27.2, RJ1.RD-, U2.22 (RX-)
RX_P: R26.2, RJ1.RD+, U2.23 (RX+)
TXD0: JP2.1, R19.1, U2.17 (TXD0)
TXD1: JP2.2, R17.1, U2.18 (TXD1)
TXEN: JP2.4, R16.1, U2.16 (TXEN)
TX_N: R25.2, RJ1.TD-, U2.20 (TX-)
TX_P: R8.2, RJ1.TD+, U2.21 (TX+)
USB_DET: R41.2, STM32.68 (PA9)
USB_ID: R24.2, STM32.69 (PA10)
USB_N: R2.2, STM32.70 (PA11)
USB_P: R3.2, STM32.71 (PA12)
VBAT: R38.2, STM32.6 (VBAT)
VDDA: C13.1, C22.1, L3.2, R29.1, STM32.22 (VDDA)
VDDA_PHY: C15.1, C25.1, C26.1, C27.1, C29.1, L1.1, R8.1, R25.1, R26.1, R27.1, RJ1.P4, RJ1.P5, U2.1 (VDD2A), U2.19 (VDD1A)
VDDCR: C17.1, C21.1, U2.6 (VDDCR)
VIN: D1.C (-), JP1.3, R40.1, SV2.1, SV2.2
VREF+: C28.1, R29.2, STM32.21 (VREF+)
VREF-: C28.2, R28.2, STM32.20 (VSSA)
XTAL1: C12.2, Q3.2, R4.2, U2.5 (XTAL1)
XTAL2: C11.2, Q3.1, R4.1, U2.4 (XTAL2)

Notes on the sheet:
ETH_RMII _REF_CLK
ETH _MDIO
ETH_RMII _CRS_DV
ETH _RMII_TX_EN
ETH _RMII_TXD1
ETH _MDC
ETH_RMII_RXD0
ETH _RMII_RXD1
ETH_MII_TXD3
I2C Pull Up
BOOTLOADER / USB
SWD
BOOT Mode Selection
BOOT1
BOOT0
Boot Mode
Main flash memory
System memory
Embedded SRAM
DURUM LEDLERİ
I2C3_SCL
I2C1_SCL / USART1_TX
I2C1_SDA / USART1_RX
I2C1_SCL
I2C1_SDA
I2C3_SDA
NETWORK/INTERNET
USART3_TX
USART3_RX
GND
3.3V
BOOTLOADER / USART3
USART6_TX
USART6_RX
JTAG PROGRAMLAMA SOKET
LAN SOKET
AMS1117 0.8Amper REGULATOR
STM32F407 ARM INTERNET GELİŞTİRME KARTI
